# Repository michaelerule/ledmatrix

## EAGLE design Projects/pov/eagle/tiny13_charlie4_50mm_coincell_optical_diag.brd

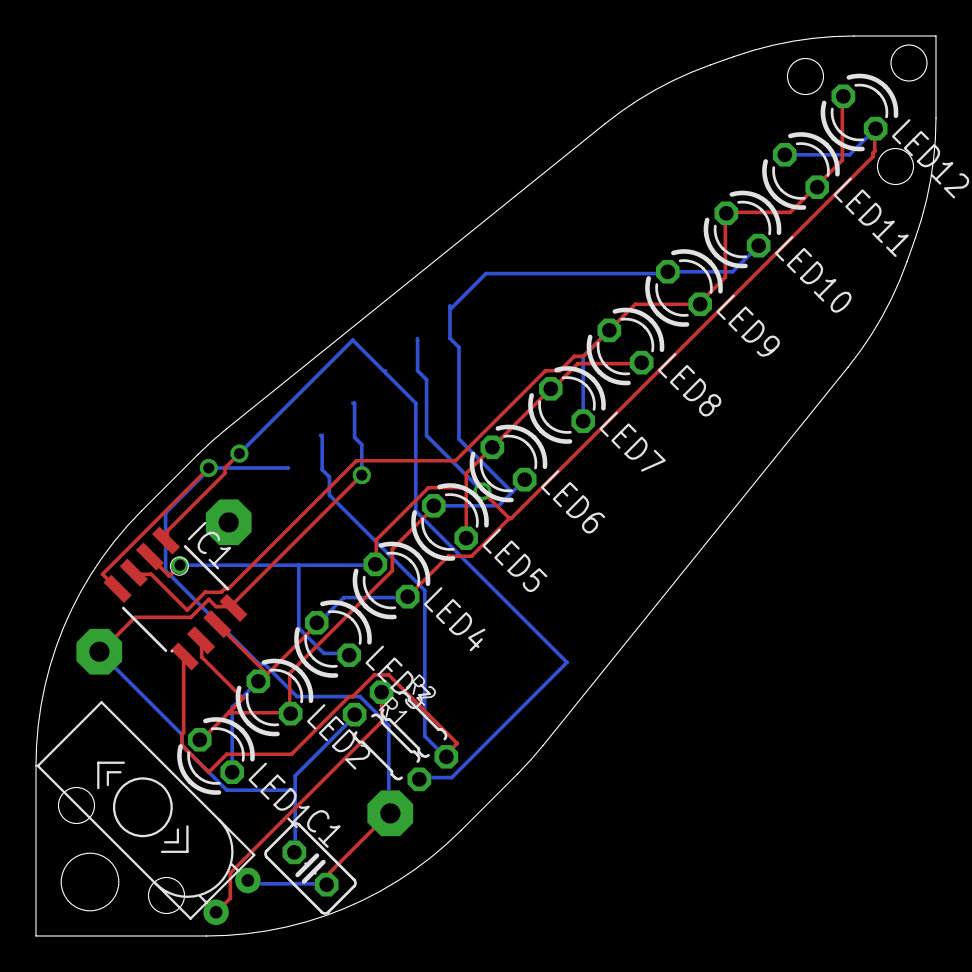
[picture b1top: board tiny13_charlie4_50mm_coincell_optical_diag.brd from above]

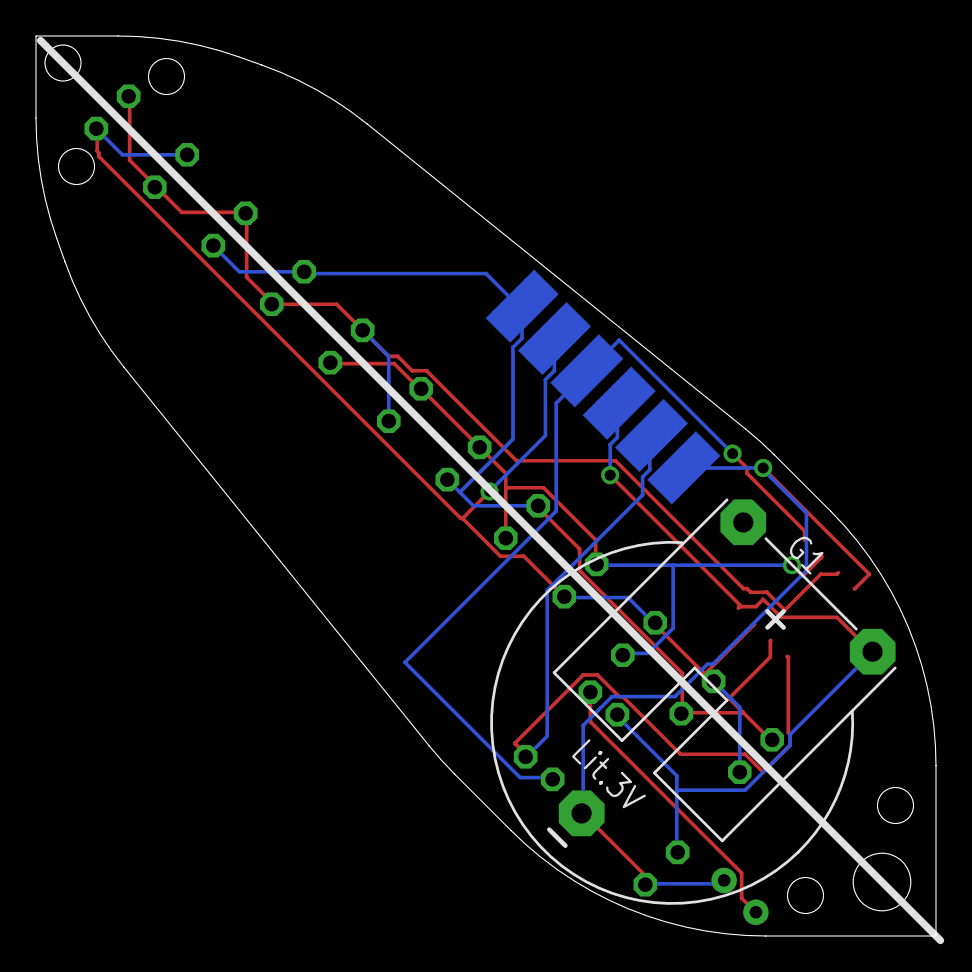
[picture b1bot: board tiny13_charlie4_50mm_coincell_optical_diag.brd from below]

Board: 2 copper layers, 50.0 x 50.0 mm, 19 parts (2 on the bottom side), 9 nets.

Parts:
C1: C025-025X050
G1: CR2032H
IC1: TINY13-20SSU; 8S1
LED1, LED2, LED3, LED4, LED5, LED6, LED7, LED8, LED9, LED10, LED11, LED12: LED3MM
R1, R2: 0204/5
U$1: TILT_SWITCH_MECHANICAL
U$2: AVR_ISP_6_PIN_1X6_SMT_CONTACT_BIG; CONTACT_ISP_PROGRAMMER_1X6_ATMEL

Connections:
GND: C1.2, G1.-, IC1.4, U$1.P$1, U$2.GND
unnamed: IC1.2, LED3.K, LED4.A, LED5.K, LED6.A, LED7.A, LED8.K
unnamed: IC1.7, LED1.K, LED2.A, LED3.A, LED4.K, LED11.A, LED12.K, U$2.SCK
unnamed: R2.1, U$1.P$2
unnamed: IC1.3, LED7.K, LED8.A, LED9.K, LED10.A, LED11.K, LED12.A
unnamed: IC1.5, R2.2, U$2.MOSI
unnamed: IC1.1, R1.2, U$2.RST
unnamed: IC1.6, LED1.A, LED2.K, LED5.A, LED6.K, LED9.A, LED10.K, U$2.MISO
VCC: C1.1, G1.+, IC1.8, R1.1, U$2.VCC

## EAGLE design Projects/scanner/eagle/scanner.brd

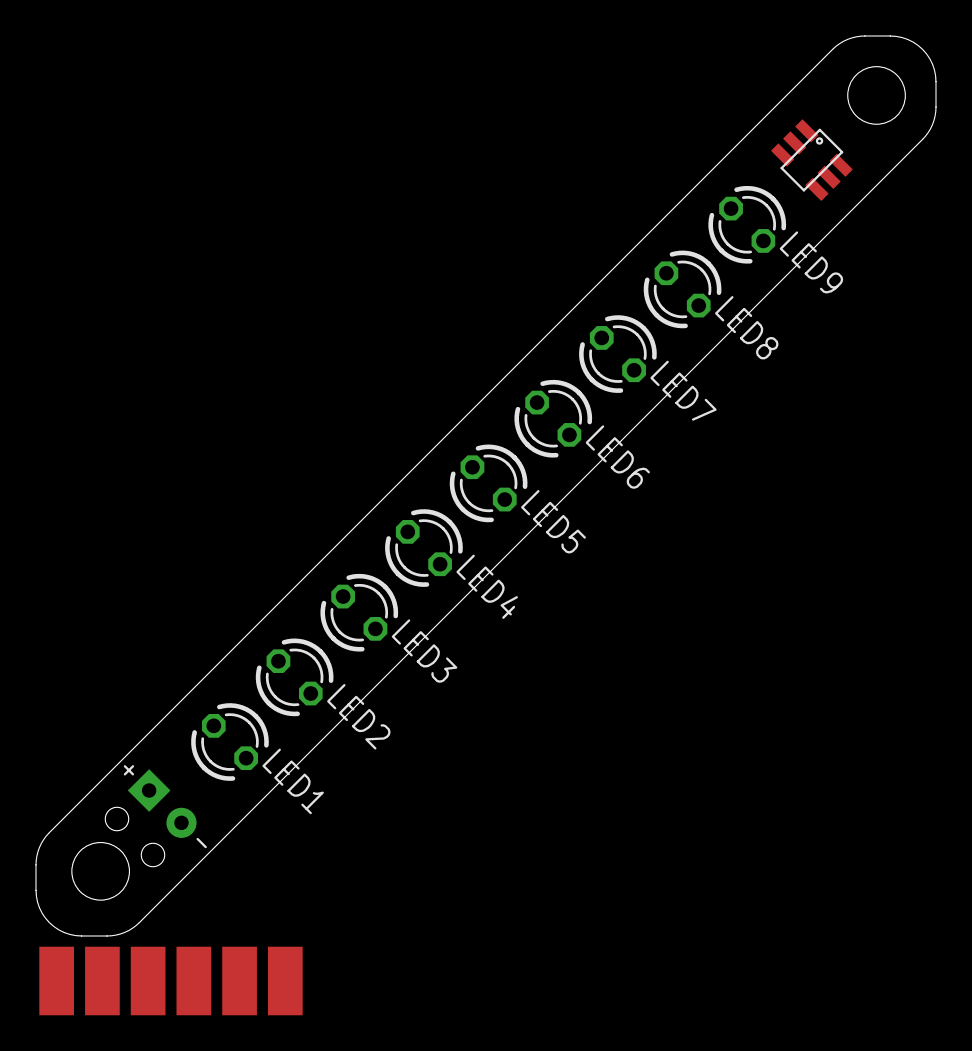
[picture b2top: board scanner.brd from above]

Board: 2 copper layers, 50.0 x 50.0 mm, 12 parts (0 on the bottom side), 6 nets, no tracks yet.

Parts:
LED1, LED2, LED3, LED4, LED5, LED6, LED7, LED8, LED9: LED3MM
U$1: ATTINY4/5/9/10; SOT23-6ST1
U$2: POWER_PINS
U$3: AVR_ISP_6_PIN_1X6_SMT_CONTACT_BIG; CONTACT_ISP_PROGRAMMER_1X6_ATMEL

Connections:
GND: U$1.P$5, U$2.P$2, U$3.GND
unnamed: LED1.A, LED2.K, LED5.A, LED6.K, LED9.A, U$1.P$1
unnamed: LED1.K, LED2.A, LED3.A, LED4.K, U$1.P$3
unnamed: LED3.K, LED4.A, LED5.K, LED6.A, LED7.A, LED8.K, U$1.P$4
unnamed: LED7.K, LED8.A, LED9.K, U$1.P$6, U$3.RST
VCC: U$1.P$2, U$2.P$1, U$3.VCC

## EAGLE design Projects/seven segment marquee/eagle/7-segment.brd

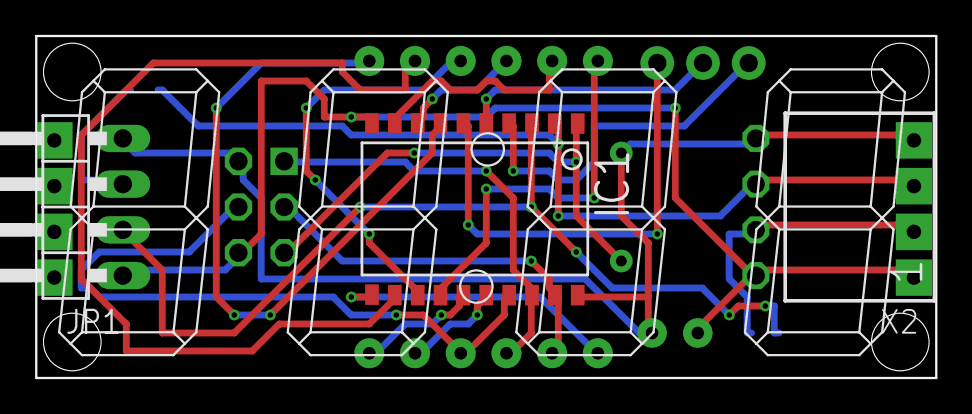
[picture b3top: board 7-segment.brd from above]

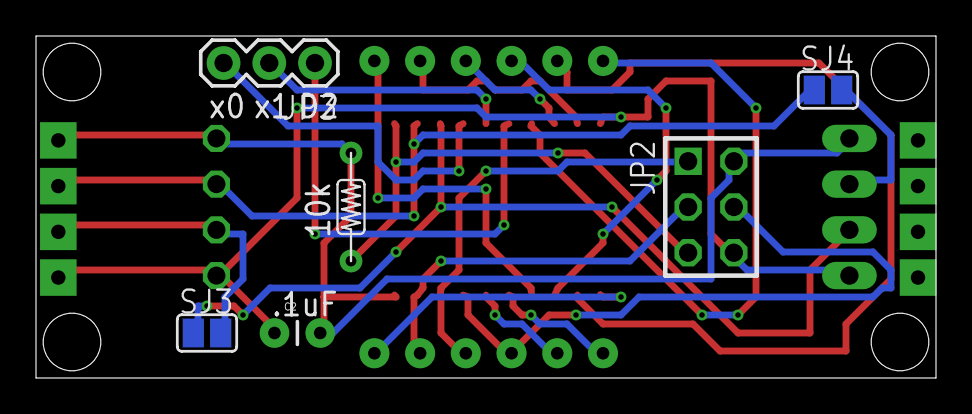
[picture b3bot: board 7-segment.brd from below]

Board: 2 copper layers, 50.0 x 19.0 mm, 18 parts (6 on the bottom side), 22 nets.

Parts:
C2: CAP-PTH-SMALL
IC1: AT90S2313S; SO20L
JP1: 1X04/90
JP2: AVR-ISP-6
JP3: 1X03
SJ3, SJ4: SJ
U$1: 7-SEGMENT-DISPLAY-5462-BS; 7SEG_5462BS
U$2: R-6
U$3, U$4, U$5, U$6, U$7, U$8, U$9, U$10: WIREPAD_SQUARE_1
X2: SSW-104-02-S-S-RA

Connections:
unnamed: IC1.15, U$1.C4
unnamed: IC1.16, U$1.C6
unnamed: IC1.17, JP2.4, U$1.C7
unnamed: IC1.18, JP2.1, U$1.C5
unnamed: IC1.19, JP2.3, U$1.C3
unnamed: IC1.11, U$1.A3
unnamed: IC1.7, U$1.A0
unnamed: IC1.12, U$1.C0
unnamed: IC1.13, U$1.C1
unnamed: IC1.8, U$1.A1
unnamed: IC1.9, U$1.A2
unnamed: IC1.14, U$1.C2
unnamed: C2.2, IC1.20, JP1.4, JP2.2, U$2.P$2, U$6.P$1, U$7.P$1, X2.4
unnamed: C2.1, IC1.10, JP1.1, JP2.6, U$3.P$1, U$10.P$1, X2.1
unnamed: SJ3.2, U$9.P$1, X2.2
unnamed: JP1.3, SJ4.2, U$5.P$1
unnamed: IC1.2, SJ4.1, U$8.P$1, X2.3
unnamed: IC1.1, JP2.5, U$2.P$1
unnamed: IC1.3, JP1.2, SJ3.1, U$4.P$1
PD2: IC1.6, JP3.1
XTAL0: IC1.4, JP3.3
XTAL1: IC1.5, JP3.2

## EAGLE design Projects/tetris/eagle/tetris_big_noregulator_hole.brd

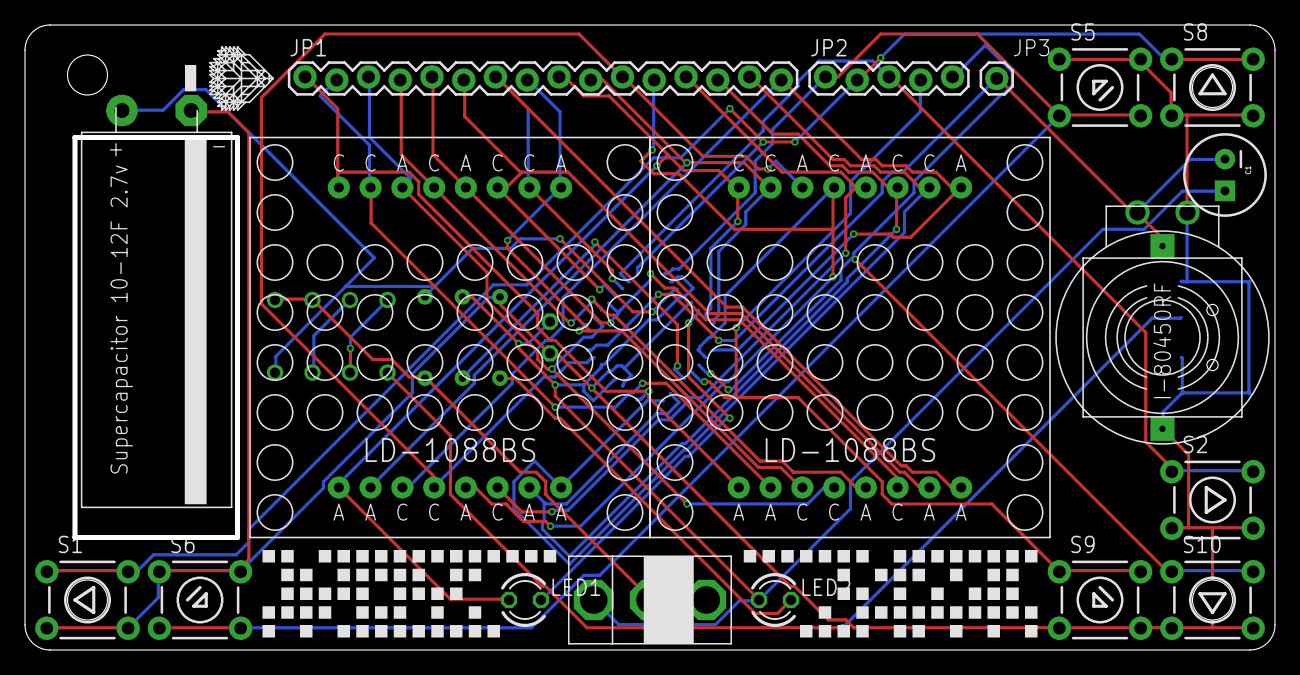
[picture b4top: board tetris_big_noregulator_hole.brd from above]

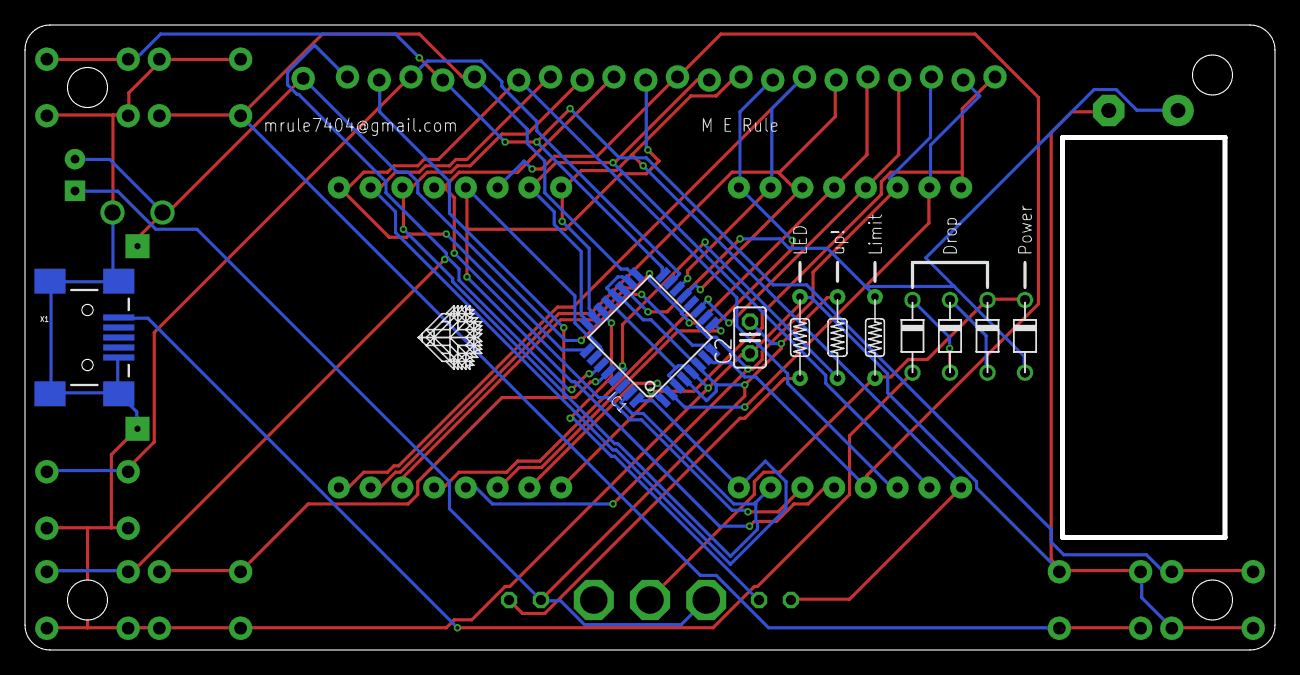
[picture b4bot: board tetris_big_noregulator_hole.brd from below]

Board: 2 copper layers, 100.0 x 50.0 mm, 31 parts (11 on the bottom side), 32 nets.

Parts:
C1: CPOL-RADIAL-100UF-25V
C2: C025-025X050
IC1: MEGA8-AI; TQFP32-08
JP1: M16LOCK; 1X16_LOCK
JP2: 1X05_LOCK
JP3: M01PTH; 1X01
LED1, LED2: LED3MM
S1, S2, S5, S6, S8, S9, S10: TACTILE-PTH
U$1, U$2: LD-1088BS
U$3, U$6: LOGO
U$4: I-80450RF; ISK4.1K_I-80450RF_I2G
U$5: NICHICON_12F; NICHICON_10X30
U$7: PIEZO_ROUND_PTH; PIEZO_ROUND_ENCASED_PTH
U$8, U$10, U$11: R-7
U$9: SPST_BIG_PTH; SWITCH_BIG
U$13, U$14, U$15, U$16: D-6; D-7.5
X1: USB-MINIB-5PIN; USB-MINIB

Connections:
GND: C2.1, IC1.3, IC1.5, IC1.21, S1.3, S1.4, S2.3, S2.4, S5.1, S5.2, S6.1, S6.2, S8.3, S8.4, S9.3, S9.4, S10.3, S10.4, U$4.P$2, U$5.P$1, U$7.P$2, U$11.P$2, X1.GND, X1.MTN1, X1.MTN2, X1.MTN3, X1.MTN4
unnamed: IC1.32, JP1.15, U$1.A4, U$2.C1
unnamed: IC1.31, JP1.14, U$1.A5, U$2.C2
unnamed: IC1.30, JP1.13, U$1.C6, U$2.A2
unnamed: IC1.26, JP1.12, U$1.A6, U$2.C3
unnamed: IC1.7, JP1.11, U$1.C7, U$2.A3
unnamed: IC1.24, JP1.10, U$1.A7, U$2.C4
unnamed: IC1.23, JP1.9, LED1.A, U$1.A8, U$2.C5
unnamed: IC1.25, JP1.16, U$1.C8, U$2.A1
unnamed: U$15.A, X1.VBUS
unnamed: IC1.13, JP1.6, U$1.C2, U$2.A5
unnamed: IC1.12, JP1.5, U$1.A2, U$2.C6
unnamed: IC1.11, JP1.4, U$1.C3, U$2.A6
unnamed: IC1.10, JP1.3, U$1.A3, U$2.C7
unnamed: IC1.9, JP1.8, U$1.A1, U$2.C8
unnamed: IC1.2, JP1.2, U$1.C4, U$2.A7
unnamed: IC1.1, JP1.1, U$1.C5, U$2.A8
unnamed: C1.2, IC1.8, JP3.1, U$4.P$1, U$7.P$1
unnamed: U$14.A, U$15.C
unnamed: IC1.29, U$10.P$1
unnamed: IC1.27, JP2.5, S10.1, S10.2
unnamed: IC1.28, JP2.4, S9.1, S9.2
unnamed: IC1.15, JP2.3, S2.1, S2.2
unnamed: IC1.16, JP2.2, S1.1, S1.2, S8.1, S8.2
unnamed: U$8.P$2, U$9.P$2, U$13.C, U$16.C
unnamed: IC1.19, U$5.P$2, U$8.P$1, U$16.A
unnamed: IC1.17, JP2.1, S5.3, S5.4, S6.3, S6.4
unnamed: U$13.A, U$14.C
unnamed: IC1.14, JP1.7, U$1.C1, U$2.A4
unnamed: LED2.K, U$11.P$1
unnamed: IC1.22, LED1.K
VCC: C1.1, C2.2, IC1.4, IC1.6, IC1.18, IC1.20, LED2.A, U$9.P$1, U$10.P$2

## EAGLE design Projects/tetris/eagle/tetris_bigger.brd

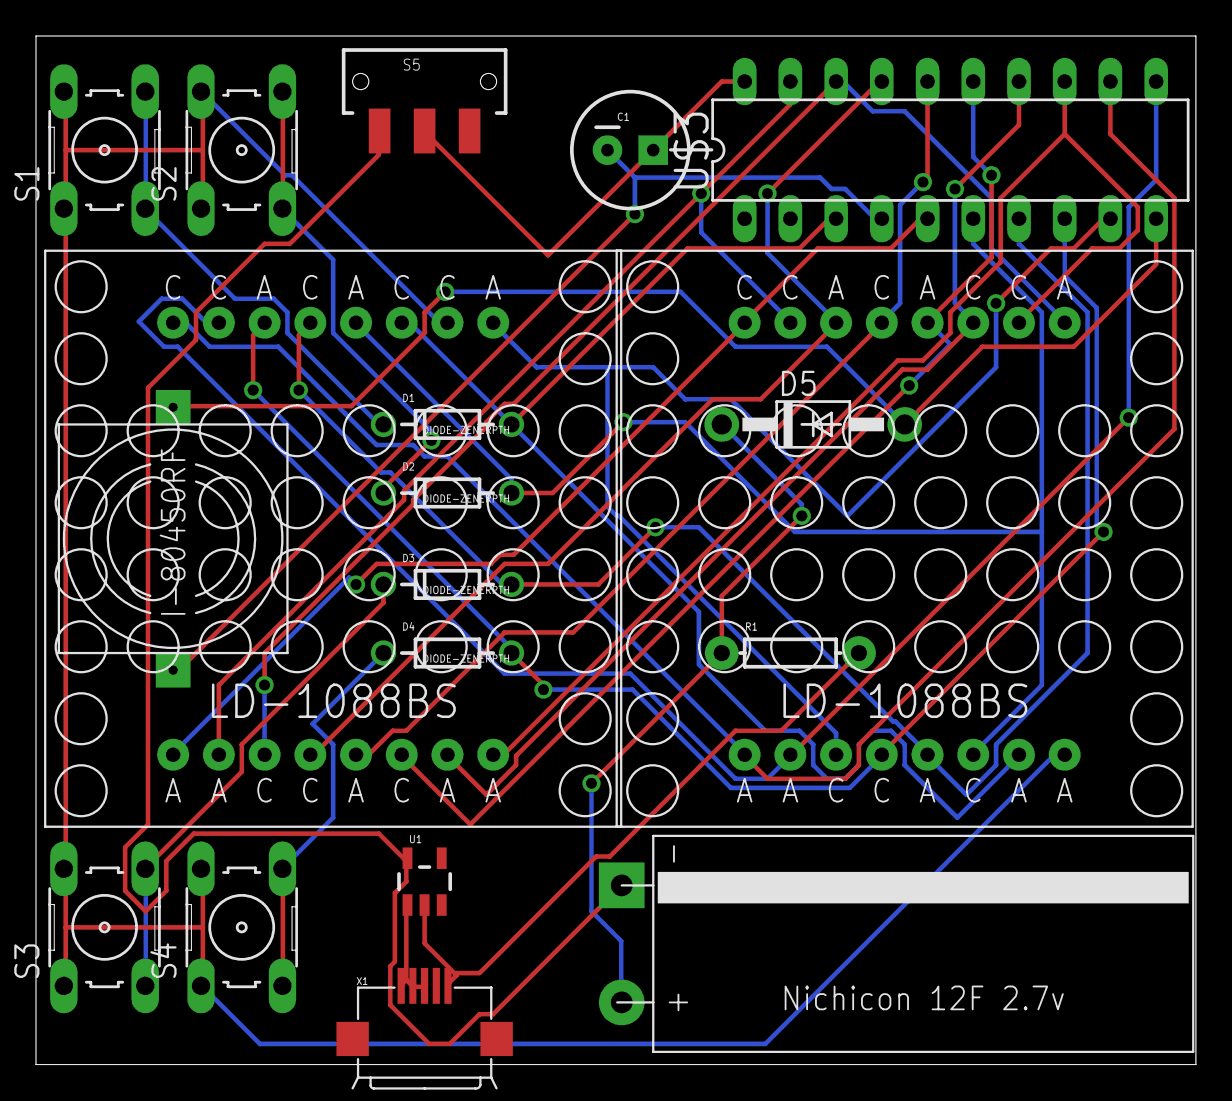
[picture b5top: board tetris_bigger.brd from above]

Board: 2 copper layers, 64.4 x 57.1 mm, 19 parts (0 on the bottom side), 27 nets.

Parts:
C1: CPOL-RADIAL-100UF-25V
D1, D2, D3, D4: DIODE-ZENERPTH; DIODE-ZENER
D5: 1N4004; DO41-10
R1: AXIAL-0.3
S1, S2, S3, S4: B3F-10XX
S5: SWITCH-SPDT-SMD
U1: V_REG_LDOSMD; SOT23-5
U$1, U$2: LD-1088BS
U$3: TINY2313-*P*; DIL20
U$4: I-80450RF; ISK4.1K_I-80450RF_I2G
U$5: NICHICON_12F; NICHICON_10X30
X1: USB-MICROB

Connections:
unnamed: U$1.A4, U$2.C1, U$3.13
unnamed: U$1.A5, U$2.C2, U$3.14
unnamed: U$1.C6, U$2.A2, U$3.15
unnamed: U$1.A6, U$2.C3, U$3.16
unnamed: U$1.C7, U$2.A3, U$3.17
unnamed: U$1.A7, U$2.C4, U$3.19
unnamed: U$1.A8, U$2.C5, U$3.5
unnamed: U$1.C8, U$2.A1, U$3.18
unnamed: D5.C, R1.P$1, U$5.P$2
unnamed: D1.P$2, U$1.C2, U$2.A5, U$3.3
unnamed: D2.P$2, U$1.A2, U$2.C6, U$3.6
unnamed: D3.P$2, U$1.C3, U$2.A6, U$3.7
unnamed: D4.P$2, U$1.A3, U$2.C7, U$3.8
unnamed: U$1.A1, U$2.C8, U$3.9
unnamed: U$1.C4, U$2.A7, U$3.11
unnamed: U$1.C5, U$2.A8, U$3.12
unnamed: C1.2, U$3.4, U$4.P$1
unnamed: D5.A, U$3.10, U$4.P$2
unnamed: S5.1, U1.5, U$5.P$1
unnamed: D1.P$1, S1.3, S1.4
unnamed: D2.P$1, S2.3, S2.4
unnamed: D3.P$1, S3.3, S3.4
unnamed: D4.P$1, S4.3, S4.4
unnamed: R1.P$2, U1.2, X1.GND
unnamed: U1.1, X1.D+, X1.D-, X1.VBUS
unnamed: C1.1, S5.2, U$3.20
unnamed: S1.1, S1.2, S2.1, S2.2, S3.1, S3.2, S4.1, S4.2, U$1.C1, U$2.A4

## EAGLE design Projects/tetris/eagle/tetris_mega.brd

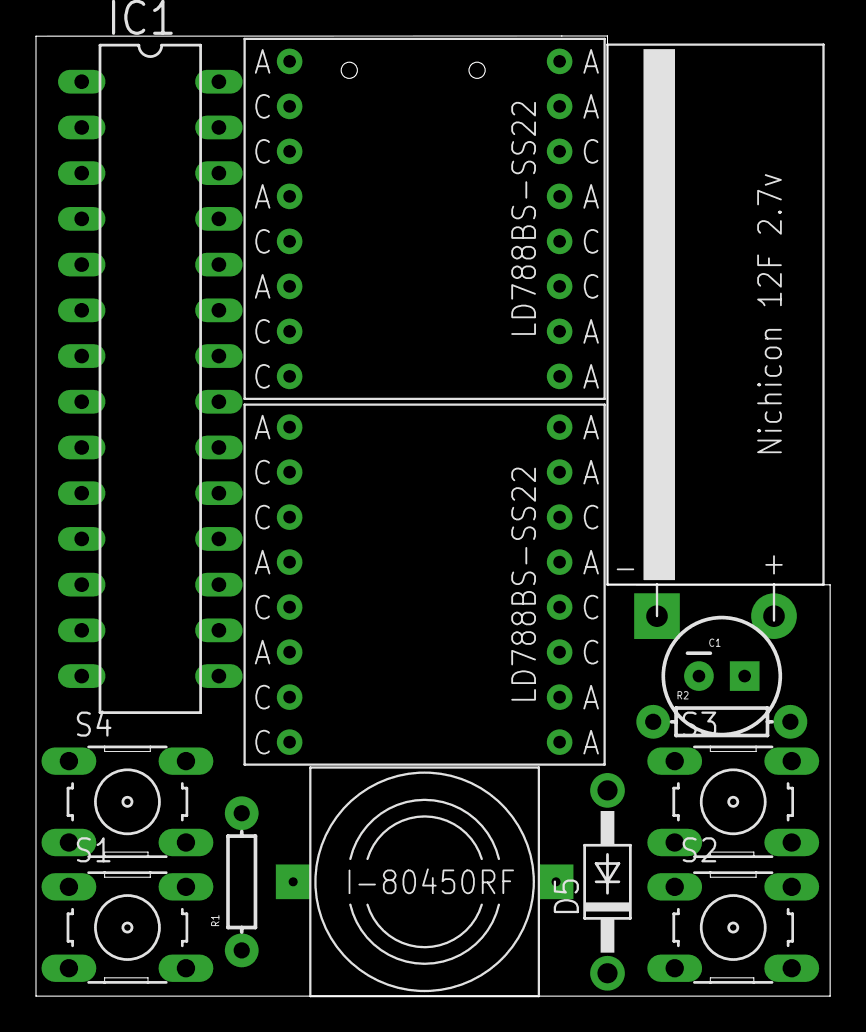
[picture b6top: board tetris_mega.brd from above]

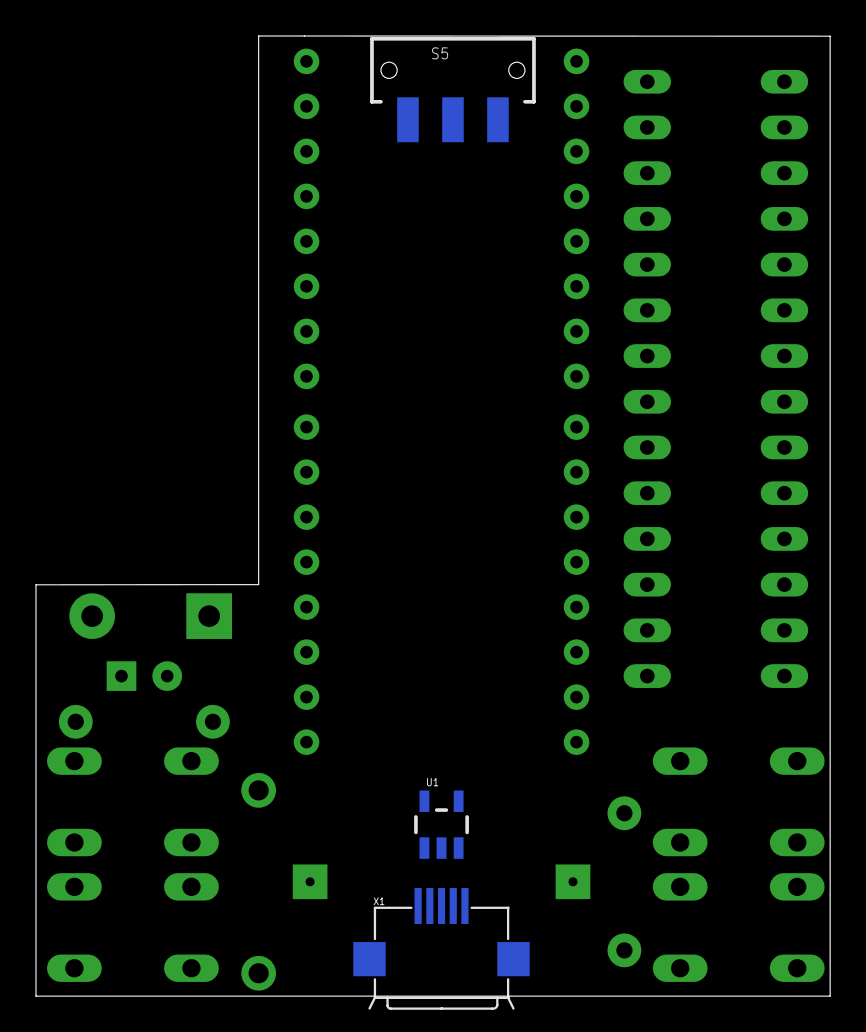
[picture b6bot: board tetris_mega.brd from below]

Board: 2 copper layers, 44.1 x 53.3 mm, 16 parts (3 on the bottom side), 28 nets, no tracks yet.

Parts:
C1: CPOL-RADIAL-100UF-25V
D5: 1N4004; DO41-10
IC1: MEGA8-P; DIL28-3
R1, R2: AXIAL-0.3
S1, S2, S3, S4: B3F-10XX
S5: SWITCH-SPDT-SMD
U1: V_REG_LDOSMD; SOT23-5
U$1, U$2: LD788BS-SS22
U$4: I-80450RF; ISK4.1K_I-80450RF_I2G
U$5: NICHICON_12F; NICHICON_10X30
X1: USB-MICROB

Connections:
unnamed: IC1.4, U$1.A4, U$2.C1
unnamed: IC1.3, U$1.A5, U$2.C2
unnamed: IC1.2, U$1.C6, U$2.A2
unnamed: IC1.26, U$1.A6, U$2.C3
unnamed: IC1.9, U$1.C7, U$2.A3
unnamed: IC1.24, U$1.A7, U$2.C4
unnamed: IC1.23, U$1.A8, U$2.C5
unnamed: IC1.25, U$1.C8, U$2.A1
unnamed: D5.C, R1.P$1, U$5.P$2
unnamed: IC1.15, U$1.C2, U$2.A5
unnamed: IC1.14, U$1.A2, U$2.C6
unnamed: IC1.13, U$1.C3, U$2.A6
unnamed: IC1.12, U$1.A3, U$2.C7
unnamed: IC1.11, U$1.A1, U$2.C8
unnamed: IC1.6, U$1.C4, U$2.A7
unnamed: IC1.5, U$1.C5, U$2.A8
unnamed: C1.2, IC1.10, IC1.22, U$4.P$1
unnamed: S5.1, U1.5, U$5.P$1
unnamed: IC1.27, S1.3, S1.4
unnamed: IC1.28, S2.3, S2.4
unnamed: IC1.17, S3.3, S3.4
unnamed: IC1.18, S4.3, S4.4
unnamed: R1.P$2, U1.2, X1.GND
unnamed: U1.1, X1.D+, X1.D-, X1.VBUS
unnamed: C1.1, IC1.7, IC1.20, IC1.21, R2.P$2, S5.2
unnamed: D5.A, IC1.8, S1.1, S1.2, S2.1, S2.2, S3.1, S3.2, S4.1, S4.2, U$4.P$2
unnamed: IC1.16, U$1.C1, U$2.A4
unnamed: IC1.1, R2.P$1

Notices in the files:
parts and their libraries:
SparkFun-Electromechanical: Licensing: CC v3.0 Share-Alike You are welcome to use this library for commercial purposes.
